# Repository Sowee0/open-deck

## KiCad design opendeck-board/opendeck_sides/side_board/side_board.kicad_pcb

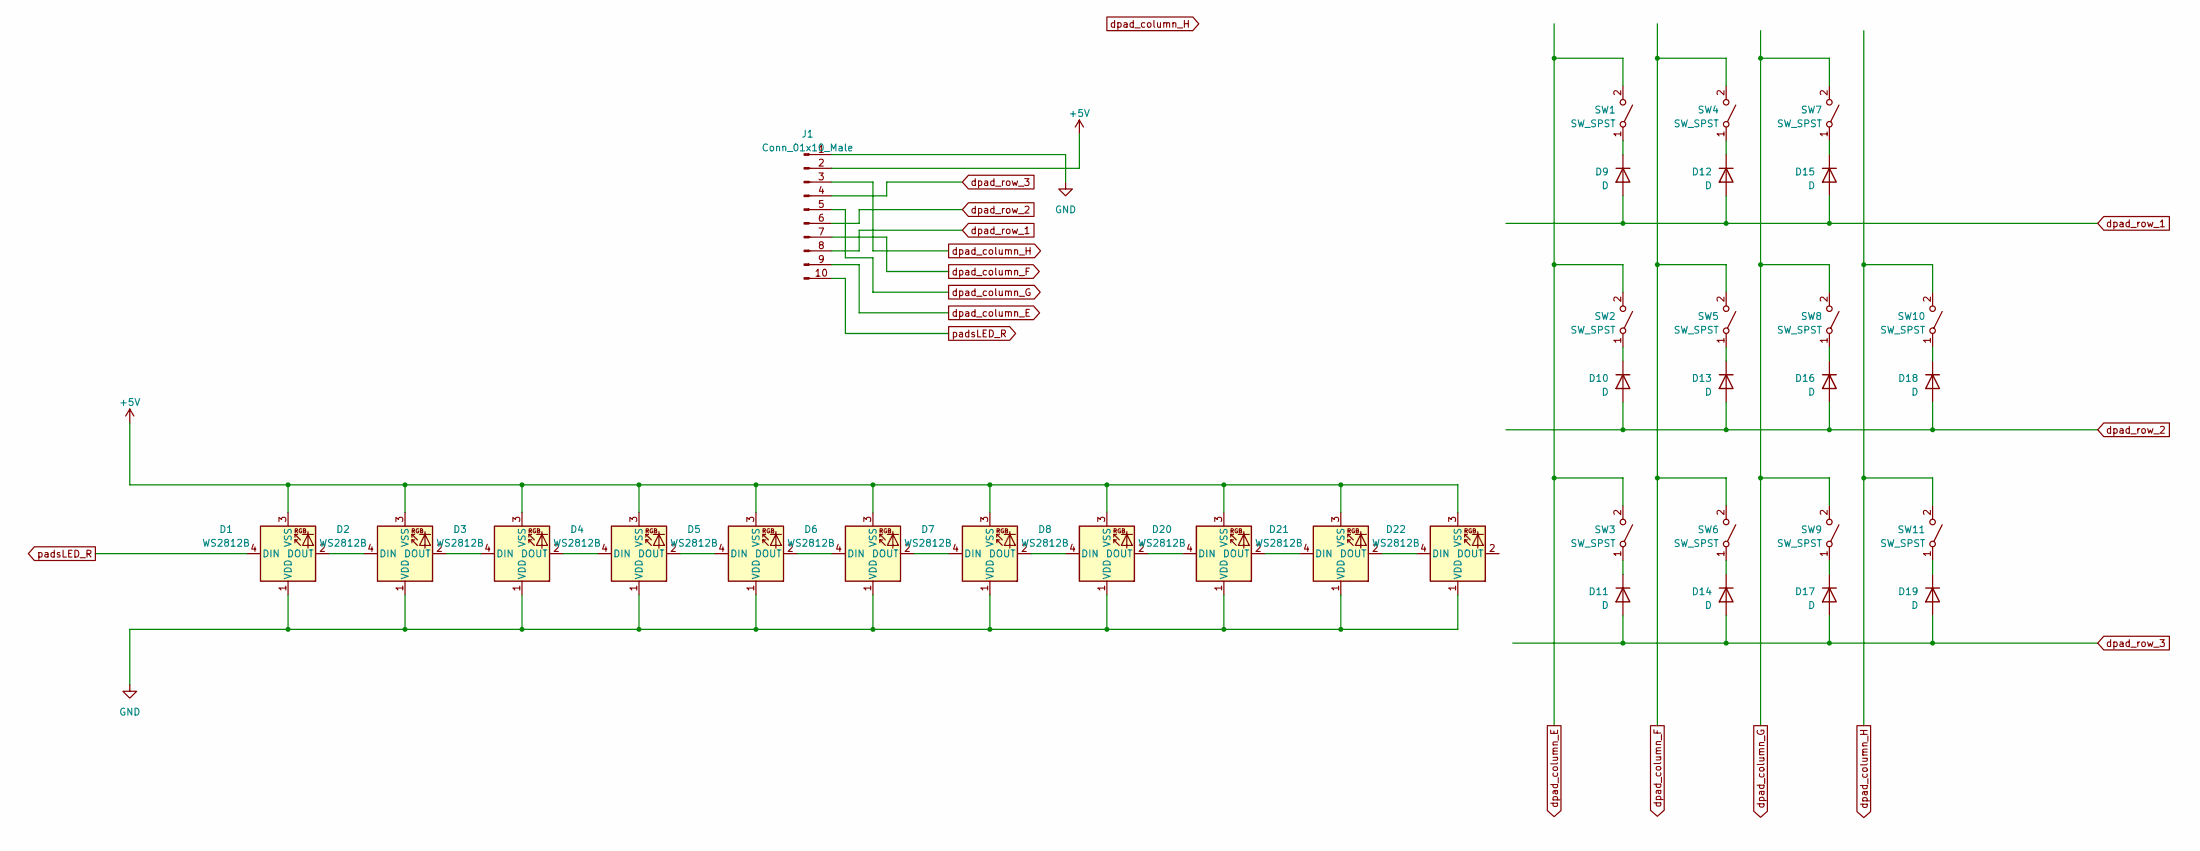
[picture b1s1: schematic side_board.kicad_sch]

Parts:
D1, D2, D3, D4, D5, D6, D7, D8, D20, D21, D22: WS2812B; LED_WS2812B_PLCC4_5.0x5.0mm_P3.2mm
D9, D10, D11, D12, D13, D14, D15, D16, D17, D18, D19: D; D_5W_P12.70mm_Horizontal
J1: Conn_01x10_Male; IDC-Header_2x05_P2.54mm_Horizontal
SW1, SW2, SW3, SW4, SW5, SW6, SW7, SW8, SW9, SW10, SW11: SW_SPST; SW_Cherry_MX_1.00u_PCB_3d

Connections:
+5V: D1.3 (VSS), D2.3 (VSS), D3.3 (VSS), D4.3 (VSS), D5.3 (VSS), D6.3 (VSS), D7.3 (VSS), D8.3 (VSS), D20.3 (VSS), D21.3 (VSS), D22.3 (VSS), J1.2
GND: D1.1 (VDD), D2.1 (VDD), D3.1 (VDD), D4.1 (VDD), D5.1 (VDD), D6.1 (VDD), D7.1 (VDD), D8.1 (VDD), D20.1 (VDD), D21.1 (VDD), D22.1 (VDD), J1.1
unnamed: D1.2 (DOUT), D2.4 (DIN)
unnamed: D2.2 (DOUT), D3.4 (DIN)
unnamed: D3.2 (DOUT), D4.4 (DIN)
unnamed: D4.2 (DOUT), D5.4 (DIN)
unnamed: D5.2 (DOUT), D6.4 (DIN)
unnamed: D6.2 (DOUT), D7.4 (DIN)
unnamed: D7.2 (DOUT), D8.4 (DIN)
unnamed: D9.1 (K), SW1.1 (A)
unnamed: D10.1 (K), SW2.1 (A)
unnamed: D11.1 (K), SW3.1 (A)
unnamed: D12.1 (K), SW4.1 (A)
unnamed: D13.1 (K), SW5.1 (A)
unnamed: D14.1 (K), SW6.1 (A)
unnamed: D15.1 (K), SW7.1 (A)
unnamed: D16.1 (K), SW8.1 (A)
unnamed: D17.1 (K), SW9.1 (A)
unnamed: D18.1 (K), SW10.1 (A)
unnamed: D19.1 (K), SW11.1 (A)
unnamed: D8.2 (DOUT), D20.4 (DIN)
unnamed: D20.2 (DOUT), D21.4 (DIN)
unnamed: D21.2 (DOUT), D22.4 (DIN)
dpad_column_E: J1.9, SW1.2 (B), SW2.2 (B), SW3.2 (B)
dpad_column_F: J1.7, SW4.2 (B), SW5.2 (B), SW6.2 (B)
dpad_column_G: J1.5, SW7.2 (B), SW8.2 (B), SW9.2 (B)
dpad_column_H: J1.3, SW10.2 (B), SW11.2 (B)
dpad_row_1: D9.2 (A), D12.2 (A), D15.2 (A), J1.8
dpad_row_2: D10.2 (A), D13.2 (A), D16.2 (A), D18.2 (A), J1.6
dpad_row_3: D11.2 (A), D14.2 (A), D17.2 (A), D19.2 (A), J1.4
padsLED_R: D1.4 (DIN), J1.10

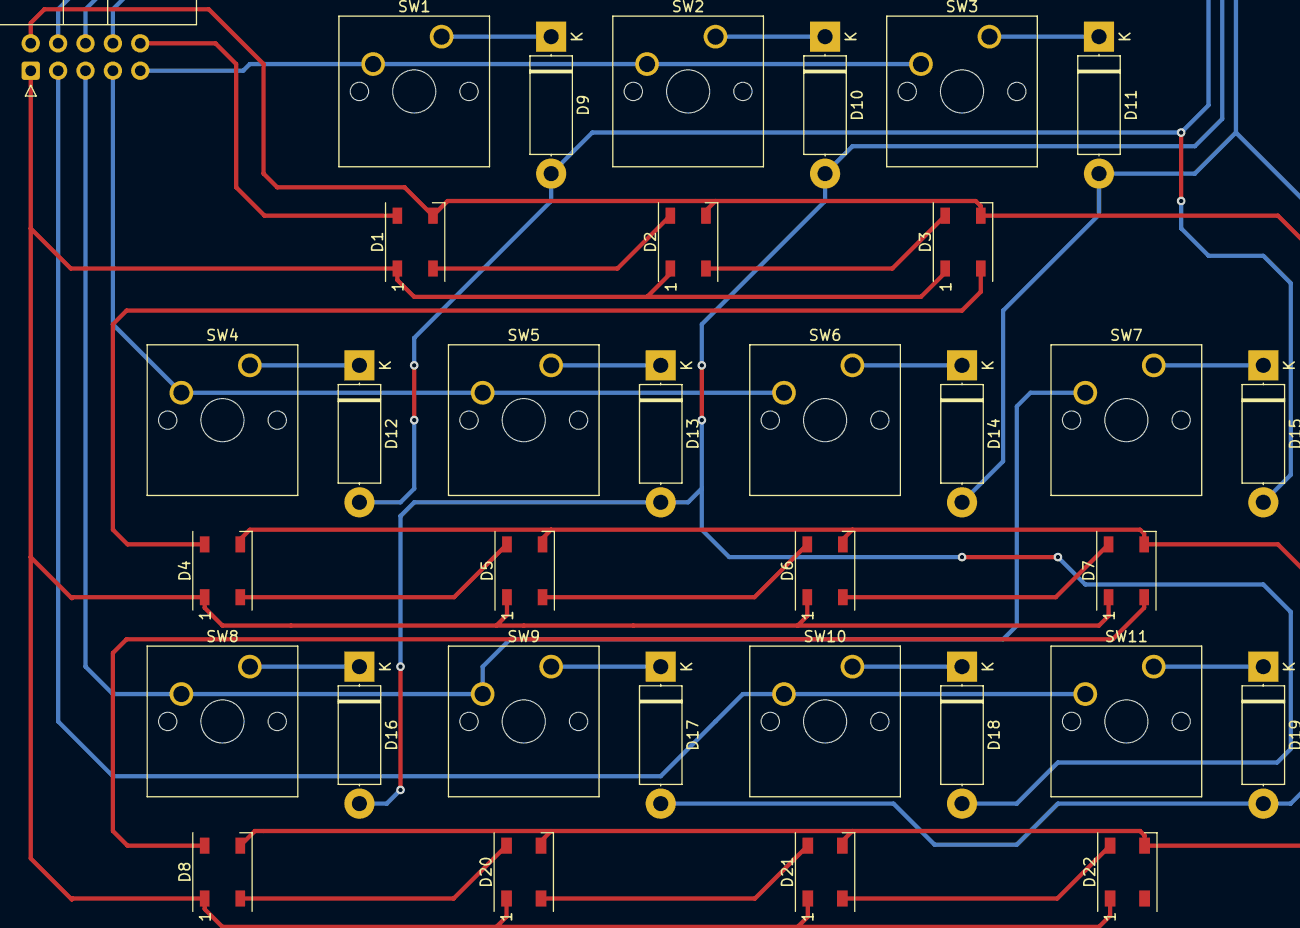
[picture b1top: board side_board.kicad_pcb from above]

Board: 2 copper layers, 34 parts (0 on the bottom side), 31 nets.

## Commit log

2023-03-07 added the matrices, leds and crossfader
2023-03-07 Adding more rows to the button matrix and moving the center module buttons to it
2023-03-10 Added the pots and keypad to the teensy
2023-03-11 starting the projects as PIO
2023-03-11 Writing the hive and worker code
2023-03-12 starting the side mounts as to make the 3d model
2023-03-14 updating to use mega
2023-03-15 Moving things around and reorganizing
2023-03-16 creating the side board
2023-03-17 updating the I2C connections on the teensy
